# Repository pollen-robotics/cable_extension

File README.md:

# cable_extension
This repository contains the KiCad project of the board used to connect the Reachy's Wrist to the rest of the arm.
It is useful for two reasons:
- It allows us to remove the wrist from the arm easily
- The wrist and the rest of the arm don't share the same 12V source so each of them has more power than if they were on the same 12V input.

## Additional Components

This PCB can't work alone, it needs a few Components soldered on it:
- 2x DF11-8DP-2DS(24) connectors
- 2x 22-05-7035 connectors

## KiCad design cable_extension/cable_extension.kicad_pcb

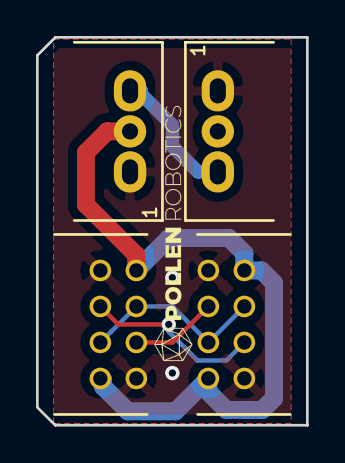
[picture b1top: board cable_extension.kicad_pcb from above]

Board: 2 copper layers, 15.0 x 21.6 mm, 4 parts (0 on the bottom side), 6 nets.

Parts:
J1, J2: DF11-8DP-2DS(24)
J3: DXL_gripper; XL320_MX_Angled
J4: DXL_arm; XL320_MX_Angled

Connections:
/DATA: J3.1, J4.1
/GND: J1.2, J1.7, J2.2, J2.7, J3.3, J4.3
/PS: J1.1, J1.8, J2.1, J2.8, J3.2
/PTP: J1.3, J1.6, J2.3, J2.6
unnamed: J1.4, J2.4
unnamed: J1.5, J2.5

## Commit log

2021-06-08 Initial commit.
